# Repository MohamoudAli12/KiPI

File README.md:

# KiPI — DC, AC and Coupled Noise Power Integrity Simulator (Standalone or KiCad Plugin)

**New to power integrity? Read the [Solver Guide](https://drewsum.github.io/KiPI/solver-guide.html)**
([source](docs/solver-guide.html)): what PI analysis is, why it matters, and how KiPI's mesh
and its DC, thermal, AC and coupled noise solvers work.

KiPI is a power and signal integrity analyzer that runs standalone or as a KiCad 9 and 10 IPC
plugin. It has four analysis modes:

* **DC: Voltage Drop.** Define voltage regulators (VRMs), loads (current into pins) and series
  parts (beads, resistors, load switches), then simulate the voltage drop net by net, across
  every copper layer. Inspect voltage, current density, via currents, copper power
  dissipation and (optionally) board temperature in a rotatable 3D view, with PASS/FAIL
  checks for loads, VRMs, vias and temperature, and write an interactive HTML report or a
  PDF.
* **AC: PDN Impedance.** Give the decoupling capacitors RLC models and put probes on a
  device's power pins, then sweep the impedance of the power distribution network (planes,
  vias, mounting and capacitors) over frequency. Check it against a flat or custom target
  impedance, with a calculator that determines the target from the load's transient spec.
* **Coupled Noise: Switcher Noise on Signal Nets.** Treat a buck or boost regulator as an
  aggressor: KiPI builds its switch node, inductor and capacitor ripple waveforms from the
  layout, then works out the noise they couple onto the signal nets you name (the victims)
  through capacitance, mutual inductance and shared ground. Each victim's receiver is
  checked against its logic family's noise margin, with the line held high and held low, and
  the 3D view shows where along its traces the noise couples in.
* **SI: Signal Integrity.** A **Quick Scan** checks every signal net in minutes: impedance
  along each trace and pair, crosstalk to its neighbours, gaps and changes in its return
  path, via stubs and pair skew. A **channel** (a net or differential pair, through its
  series parts) is extracted from field-solved cross-sections and via models into
  S-parameters, TDR, statistical and PRBS eyes with the interface's equaliser, COM, and
  waveforms with generic or IBIS buffers, each checked against the interface (USB, PCIe,
  SATA, HDMI, LVDS, DDR4 and more).

New to KiPI? The **[user guide](docs/help.html)** (also the **Help** button in KiPI, or
**F1**) walks through every button, the workflows and what the results mean. Every
control in KiPI has a tooltip. This README is an overview; the user guide has the details.

**Status: 0.9.3 (alpha, in development)** ([changelog](docs/CHANGELOG.md)). KiPI runs on its own too, with an app launcher that handles dependencies, and imports boards from other layout tools. The author wants to add support for more PCB file formats. If you have an example with good complexity which uses a wide variety of your PCB design tool's features that you are willing to share, please open an [issue](https://github.com/drewsum/KiPI/issues) and attach your PCB file there.

## Install

KiPI runs two ways, from the same folder:

* **As a KiCad plugin**, the main way: click the **KiPI** button in the PCB editor and KiPI
  reads the board open there. For this, the KiPI folder **must be in KiCad's plugins
  folder**, and KiCad installs its dependencies.
* **Standalone**: KiPI started on its own, with its launcher, opens board files and needs
  no KiCad. The folder can be **anywhere**; the launcher installs the dependencies on the
  first start. It opens KiCad 7 to 10 board files (`.kicad_pcb`), ODB++ jobs, HyperLynx
  files (`.hyp`) and KiPI snapshots (`.kipi.json.gz`). Reading CCE files is on the way
  ([#143](https://github.com/drewsum/KiPI/issues/143)).

### As a KiCad plugin

#### Requirements

* **KiCad 9.0 or later.** Developed on KiCad 10 and confirmed on KiCad 9. Before 9.0.3,
  KiCad cannot say which layers a plated pad has copper on, so pads are kept on every layer
  (KiPI warns in its log), and 9.0.0 cannot report net classes.
* **Python 3.10 to 3.13**, the one KiCad runs plugins with (some dependencies have no
  prebuilt packages for Python 3.14 yet).
  * **Windows:** KiCad's own Python 3.11. Nothing to do.
  * **Linux:** KiCad uses the system Python. On a distribution with Python 3.14 (Ubuntu
    26.04, Fedora 43), pip has to compile some packages, which needs
    `sudo apt install build-essential python3-dev` or similar.
  * **macOS:** KiCad bundles Python 3.9, which is too old. Install Python 3.12 (for
    example from python.org or Homebrew) and select it as the **Python interpreter** in
    *Preferences → Plugins*.

#### Steps

1. In KiCad, enable **Preferences → Plugins → Enable KiCad API**.
2. Clone, link (or copy) this repo into your KiCad plugins folder, or uncompress the release source zip. The examples use KiCad 10's
   folder: for KiCad 9, put `9.0` in place of `10.0`. On Windows, KiCad uses your
   *Documents* folder, which may be redirected to OneDrive:

   ```powershell
   $plug = "$([Environment]::GetFolderPath('MyDocuments'))\KiCad\10.0\plugins"
   New-Item -ItemType Junction -Path "$plug\KiPI" -Target "<path to this repo>"
   ```

   On macOS the folder is `~/Documents/KiCad/10.0/plugins`, and on Linux
   `~/.local/share/kicad/10.0/plugins`:

   ```sh
   ln -s "<path to this repo>" ~/Documents/KiCad/10.0/plugins/KiPI          # macOS
   ln -s "<path to this repo>" ~/.local/share/kicad/10.0/plugins/KiPI       # Linux
   ```

   Or, without git, download `KiPI-<version>.zip` from the
   [latest release](https://github.com/drewsum/KiPI/releases/latest) and unzip it into the
   plugins folder, which gives `plugins/KiPI`.

3. Restart the PCB editor. KiCad builds the plugin venv in the background; the first time this
   downloads PySide6 and VTK, so give it a few minutes. The **KiPI** toolbar button appears
   once the venv is ready. If it never appears, right-click the action in
   *Preferences → Plugins* and choose *Recreate Plugin Environment*.

### Standalone

1. Install **Python 3.10 to 3.13** if you do not have one (from
   [python.org](https://www.python.org/downloads/), or your package manager). On Linux, add
   `python3-venv` (Debian, Ubuntu) and, for the setup window, `python3-tk`.
2. Put the KiPI folder anywhere: clone this repo, or unzip `KiPI-<version>.zip` from the
   [latest release](https://github.com/drewsum/KiPI/releases/latest).
3. Start KiPI with its launcher: double-click **`kipi_launcher.pyw`** (Windows), or run

   ```sh
   python kipi_launcher.py                      # or: python kipi_launcher.py <board>.kipi.json.gz
   ```

   On Windows the first start leaves a **KiPI** shortcut next to it. On Linux and macOS, run
   `python3 kipi_launcher.py --create-shortcut` once to add KiPI to the applications menu
   (Linux) or `~/Applications` (macOS).

The first start sets up KiPI. The setup window lists every package KiPI will install with
its size (about 254 MB to download on Windows), and nothing is installed until you click
**Install**. On Windows and Linux x86-64 it also offers
[PARDISO](#optional-faster-solves-on-large-boards-windows-and-linux-x86-64). Everything goes
into an environment of KiPI's own, outside the KiPI folder (`KIPI_HOME` puts it elsewhere):

| | KiPI's environment |
|---|---|
| Windows | `%LOCALAPPDATA%\KiPI` |
| macOS | `~/Library/Application Support/KiPI` |
| Linux | `~/.local/share/kipi` |

Use **Open…** to open a board and **Reload** to read it again. KiCad boards keep the same
setup file standalone and in the plugin. KiPI uses the zone fills saved in the file, so
**fill the zones in KiCad (B) and save** before opening a `.kicad_pcb`. ODB++ jobs and
HyperLynx files share a board's setup when exported next to it with the same name
(`Board.zip`, `Board.hyp`). The [user guide](docs/help.html) lists what each format does
and does not carry.

To change the setup later, use **About → Manage dependencies…** in KiPI, or the launcher:

```sh
python kipi_launcher.py --setup              # the setup window again (add or remove PARDISO)
python kipi_launcher.py --add-pardiso        # or --remove-pardiso, without questions
python kipi_launcher.py --repair             # reinstall everything from scratch
python kipi_launcher.py --reset              # delete KiPI's environment
python kipi_launcher.py --create-shortcut    # add KiPI to the Start menu / app menu / ~/Applications
```

If setup fails, the launcher says why; everything the installer printed is in the `logs`
folder next to the environment.

### Optional: faster solves on large boards (Windows and Linux, x86-64)

If the optional [`pypardiso`](https://pypi.org/project/pypardiso/) package is installed,
KiPI solves with Intel MKL's multithreaded PARDISO solver in place of SciPy's
single-threaded one. On a 645k-unknown rail one solve drops from about 8 s to 1.2 s. Small
boards gain little. It costs about 210 MB of download on Windows (320 MB on Linux) and
there are no MKL packages for macOS or ARM.

The KiCad plugin gets it with its other requirements, installed by KiCad into the plugin's
environment. Standalone, the launcher's first setup installs it by default, with an
opt-out. *About → Manage dependencies…* adds or removes it later (in the plugin, removed it
is also left unused, since KiCad puts it back when it reloads the plugin), and *About → Copy version info* shows which solver is in use. If
PARDISO cannot load, KiPI falls back to SciPy and says so in the log.

## Using KiPI

### 1. Open your board in KiCad

Open your board in the PCB editor and click the **KiPI** toolbar button. KiPI opens in its
own window and reads the board through the KiCad API; the log at the bottom streams each
stage as it runs.

* **Load from KiCad** re-reads the board after you edit it in KiCad, and reloads the saved PI setup.
* **Refill zones** (on by default) refills every zone in KiCad before reading, so the zone
  fills KiPI sees match your current routing. KiPI analyzes filled copper only.
* **Save snapshot… / Open snapshot…** store the extracted board as a file that KiPI can open
  later without KiCad. See example snapshots in the repo to experiment!
* **Power Integrity: DC / AC / Noise** and **Signal Integrity: SI** (the start of the
  toolbar, or **Ctrl+1** to **Ctrl+4**) pick the analysis mode. Readme sections 2 to 5 are DC, the default;
  [section 6](#6-ac-pdn-impedance) covers AC, [section 7](#7-coupled-noise) Coupled Noise and
  [section 8](#8-signal-integrity) Signal Integrity. The VRMs, series links and capacitor
  models are shared by the power modes.
* **Help** (or **F1**) opens the [user guide](docs/help.html) in your browser.

### 2. Pick Power Nets from Netlist

The **Board** panel on the left lists every net in the extracted design. Tick the nets you
want to analyze: only ticked nets can be simulated, and they are offered in the PI setup pin
pickers. **Power & ground only**, **All power** and **None** help pick them, and the ticks
are saved with the setup.

Below that are the **Copper layers**, the **Display** options (color by layer or net, Z
scale, vias, pads, mask, silkscreen, part **3D Models**), and **PI Models**, which marks the
parts of the current analysis in 3D. Clicking a part in 3D selects it in the setup, and the
**Info** box shows whatever you last clicked, with **Select in KiCad** to find it in the PCB
editor.

The **Power tree** toolbar button opens a block diagram of the modelled power network, left
to right in the direction power flows, and can be saved as a PNG.

The **Stackup** toolbar button lists every copper and dielectric layer with its thickness,
material, εr, thermal conductivity and resistivity, with a cross-section drawn to scale.
Untick **Lock to imported values** to try other thicknesses and materials: every analysis
uses the edited stackup.

Drag to rotate, scroll to zoom and shift-drag (or middle-drag) to pan; the
[user guide](docs/help.html#keys) lists every keyboard shortcut.

### 3. Model the Power Distribution System

The **PI setup** panel on the right holds the power tree. Each list has **Add**,
**Duplicate** and **Remove** buttons, and every field has a tooltip. Pins are chosen with a
picker: the net, then the part, then optionally the pin numbers. As you pick pins, KiPI
pre-fills what usually follows from them (a VRM's target voltage from the net name, ground
pins, a series link's other side and a resistor's value), and problems are shown in red.
**Import…** fills the power tree from a Tomachie power-tree file (`<design>.pdn.json`).

**VRMs tab**: one entry per regulator, power input, or ideal supply. A VRM is a **Source**,
**LDO**, **Switcher** or **Isolated** converter, with its output pins and target voltage,
its input pins (which link it to the rail upstream), efficiency or quiescent current, and
optional remote sense, ground pins, load line, dropout, input range, DC accuracy, current
limit and multiple **Phases**. KiPI works out each VRM's input current from what it feeds.

To try it without a design of your own, open the example board in
[`examples/multiphase_buck`](examples/multiphase_buck): a 4-phase 12 V → 0.9 V, 40 A core rail
(`python -m kipi --snapshot examples/multiphase_buck/multiphase_buck.kipi.json.gz`).

**Loads tab**: one entry per consumer: its **Supply pins**, **Current** (split evenly or by
pin group), optional **Ground pins** and a **Tolerance** for PASS/FAIL. **Load models**
(**Model ▾**) save and apply a part's supplies as a YAML file.

**Series links tab**: parts that pass DC from one net to another, such as sense
resistors, ferrite beads, fuses, load switches and 0 Ω links: **Side A pins**, **Side B
pins** and a **Resistance**. **Import SPICE model…** uses the maker's SPICE model of the part
for both DC and AC, including diodes and multi-pin parts such as common-mode chokes.
**In order to assign a series link, the nets on either side must both be defined as power
nets in the net selection pane.**

**Solve tab**: every combined rail, with a checkbox. Untick the rails that are not modeled or
routed yet to solve the rest.

**Mesh tab**: **Max edge** is the largest FEA mesh triangle edge in mm; smaller is more
accurate and slower. **Via plating** sets each kind of via's plating thickness and fill.

**Thermal tab** (off by default): tick **Electro-thermal co-simulation** to make losses heat
the board and the warmer copper become more resistive. Each copper layer has its own
temperature, with heat crossing the laminate and running down vias. Inspired by
[KiCad Thermal Sim](https://github.com/PoeAlex/KiCad_Thermal_Sim) by
[PoeAlex](https://github.com/PoeAlex).

The setup is saved as `<board>.kipi-setup.yml` next to the board when you click **Save** and
every time you solve. It travels with the project and can go into version control. AI agents
can make quick work of power tree modelling by editing this file directly.

### 4. Solve

Click **Solve all**. Every rail is meshed and solved, downstream loads first, so each VRM's
input current includes everything it feeds. Progress streams into the log; **Cancel** stops
the run.

Click **Report** to write an HTML report next to the board, or choose **PDF**. The HTML
report is a single portable file with the summary and every results table, an interactive 3D
view per rail, per-layer voltage and current-density maps, the board temperature map when
thermal is on, and a **User notes** box.

| Summary tables | Interactive 3D per net group |
|---|---|
|  |  |

### 5. Read the results

In the **Results** pane, choose a **net group** and a **field** to show in 3D: **Voltage**,
**Current density** (tick **Arrows** to see the flow), **Power density**, **Via current**
or **Temperature**. Click any point to probe it in the Info box, and set the **Color
scale** to look closer.

| Via current | Temperature |
|---|---|
|  |  |

The result tabs give **Loads** (effective voltage, drop and PASS/FAIL), **VRMs**, **Series
links** (I²R losses), **Vias** ranked by current, **Losses**, **Thermal** and **Notes**.
**Export ▾** writes CSV or ParaView files, and **Save results…** writes a results file that
**Open results…** reloads without solving again.

### 6. AC: PDN impedance

Switch **Mode** to **AC**. The **AC setup** shares the VRMs and series links with DC mode and
adds:

* **Capacitors tab**: RLC models (capacitance, ESL, ESR) for the decoupling capacitors, each
  shared by a group of identical parts, or the maker's SPICE model. **Models from values**
  starts one model per capacitor value. Models can be derated for DC bias, temperature,
  aging and tolerance. **Important**: model capacitors of the same value in different case
  sizes separately.
* **Probes tab**: where to plot the PDN impedance, usually a device's supply and ground pins,
  each with a **flat** or **custom** target. The **Target Impedance/Frequency Calculator**
  works out a flat target from the device's voltage tolerance and load step, following Smith
  et al., ["Power Distribution System Design Methodology and Capacitor Selection for Modern
  CMOS Technology"](https://doi.org/10.1109/6040.784476), IEEE Trans. Adv. Packaging, 1999.
  Targets apply above the VRM's **Control loop bandwidth**.
* **Sweep tab**: frequency range and resolution, and the capacitor deratings.
* **Mesh tab**: mesh size and minimum edge at plated holes.

| Capacitor models | Target calculator |
|---|---|
|  |  |

Pick the **Rail** and **Ground** and click **Solve rail**. The rail's copper and its ground
are field-solved, so plane resistance, spreading inductance, plane capacitance, cavity
resonances and via inductance all come from the layout; the capacitors and series links are
attached at every frequency. The VRM is not modeled as an impedance (the open-loop PDN).
**Important:** AC analysis is a massive compute problem. Many probes and a finer mesh
increase simulation time dramatically.

The **Impedance** tab plots |Z| against frequency for every probe, with its target, and a
cursor to read values. The **Board map** tab shows the mesh, probes and capacitors, and the
**Transient** tab estimates each probe's undershoot and overshoot for its load step.
**Report**, **Export CSV…** and **Save results…** work as in DC mode.

### 7. Coupled Noise

Switch **Mode** to **Noise**. The **Coupled Noise setup** treats one of the setup's
**Switcher** VRMs as an *aggressor* and the signal nets you name as *victims*. The
screenshots below are the `examples/validation/coupled_noise` example: a 12 V to 1.8 V,
1 MHz buck over a ground plane, with three victims. Open its snapshot to try it.

* **Aggressors tab**: **Add** makes an aggressor from a switcher VRM and fills it in from the
  board: the switching device, inductor, switch node and capacitors. Give the switching
  frequency and edge times; datasheet values such as Coss and Qrr are optional. KiPI traces
  each capacitor's hot loop through the copper for its inductance and its coupling.
* **Victims tab**: each victim is a net with its driver and receiver pins and a **Type**
  (CMOS, open drain, terminated, LVDS, analog input or undriven) and **Logic level**, which
  set its loading and noise margin.
* **Capacitors tab**: the same capacitor models as AC mode.
* **Settings tab**: harmonics, damping, victim resolution and the **Board model**, the slow
  but more accurate field model of the converter's copper (untick it for a quick look).

Pick the **Aggressor** and click **Solve**. Tick **Scan nearby nets** to also check every
signal net near the aggressor. The **Waveforms** tab plots the switch node with its ringing,
the inductor and capacitor currents and the rail ripple, in time or as a spectrum.

The **Results** table lists each victim's peak noise at its receiver, its margin, the
dominant mechanism and PASS or FAIL. **Victim noise** plots the noise, as a whole or by
mechanism (capacitive, inductive, common ground).

**Victim held high and low** draws the noise riding on the receiver's high and low levels
against its thresholds.

**Coupling in 3D** colors the selected victim's traces by their share of the peak noise, so
the pieces to move stand out. **Hot loops in 3D** draws the capacitor loops' current, and
**Fields in 3D** the H and E fields over the board, with near-field hotspots and a first
radiated estimate against CISPR 32 class B. Victims crossing a split in their reference
plane are noted.

The mechanisms point to different fixes: capacitive noise comes from the switch node's
dV/dt, inductive noise from the hot loop's dI/dt and common noise from the switching
current's return. **Report** and **Save results…** work as in the other modes.

### 8. Signal Integrity

Switch **Mode** to **SI** (**Ctrl+4**). The **Signal Integrity setup** has four tabs. To
try it, open `examples/signal_integrity/signal_integrity.kipi.json.gz`: a clock net through
a series resistor and a USB pair changing layers through vias, with a channel set up for
each.

* **Quick Scan**: **Scan** cuts every signal net (or only the nets ticked in **Board**) into
  short sections and field-solves each cross-section with its neighbours. Each net gets
  PASS, WARN or FAIL for its impedance (Z0, or Zdiff for pairs found by name: `_P`/`_N`,
  `+`/`-`, `DP`/`DM`), its worst crosstalk coefficient, any length with no reference plane
  or crossing a plane's gap, layer changes without a return via nearby, via stubs that
  resonate in band, and pair skew. **Impedance in 3D** colors the traces by how far they
  are from target. **Make a channel** turns the selected net into a channel. Slow control
  nets (enables, resets, LEDs, I²C, JTAG) are left out unless **Slow nets** is ticked. Cuts
  that come out alike are solved once, in parallel on the CPU's cores: a 6-layer board with
  about 400 signal nets takes a few minutes, and a rescan seconds.
* **Channels**: a channel is a net or a pair, followed through series resistors and
  AC-coupling capacitors to its receiver. **Add bus…** makes one for each net between a
  transmitter and a receiver part (a DDR byte lane, an ADC's lanes), with the neighbours as
  aggressors. Pick its **Interface** (rate, swing, edges,
  terminations, equaliser and limits come from it, and any can be overridden) and its
  **buffers**: generic ones, or a model from a manufacturer's **IBIS** file at a corner.
  **Aggressors** add their near- and far-end crosstalk.
* **Results**: after **Solve**, the checks (impedance, insertion and return loss at
  Nyquist, mode conversion, skew, the eye against the receiver mask, COM, overshoot,
  ringback, monotonic edges, crosstalk) and the **SI plots** tab: the eye (statistical at
  the target BER with the best equaliser, or the raw or PRBS eye), TDR, S-parameters,
  waveforms at the dies and the pulse response. **Export Touchstone…** writes the channel's
  `.s2p`/`.s4p`, and **Export SPICE…** a passive rational model of it as a SPICE subcircuit
for any circuit simulator; **Report** and **Save results…** work as in the other modes.
* **Settings**: section length, etch, copper roughness (Hammerstad, Groisse or Huray), the
  sweep and the scan's limits.

### Tips and troubleshooting

* **A load shows DISCONNECTED** usually means unrouted copper, an unfilled zone, or a
  missing series link for a part between two power nets.
* **Unexpected voltage drop:** thermal reliefs, necked traces, via counts and anti-pads in
  planes dominate DC drop; the Current density view with Arrows shows the bottleneck.
* **Slow solves:** raise **Max edge**, or analyze fewer nets at a time. On Intel x86, install
  the PARDISO solver (above).
* **"KiPI works with one KiCad at a time"** although only one is open: a KiCad that did not
  exit cleanly may still be running; end it in the task manager.
* **Logs:** each session writes to `kipi/kipi-<date>-<time>-<pid>.log` in the temporary
  folder, with a matching `.crash.log`. Attach both, and **About → Copy version info**, to
  bug reports. The [user guide](docs/help.html) has more troubleshooting.
* **Have Fun:** The author asks that you share what projects this package has simulated, and what power integrity issues you have found with it. Conductor simulation gives incredible insight into how PCBs actually function in practice. See what happens when you pump 10 amps into a 5 mil trace with the temperature results view.

## Development

From a checkout, KiPI runs standalone, or as the plugin against the running PCB editor:

```powershell
python -m venv --system-site-packages .venv   # use KiCad's bundled python.exe
.venv\Scripts\pip install -r requirements.txt -r requirements-dev.txt
.venv\Scripts\python -m kipi tests\data\synthetic.kipi.json   # standalone, opening a board
$env:KIPI_HOST = "plugin"; .venv\Scripts\python -m kipi        # the plugin: connect to KiCad
.venv\Scripts\python -m kipi --dump board.kipi.json.gz   # extract from KiCad only, no window
.venv\Scripts\python -m pytest tests
.venv\Scripts\ruff check .                    # lint, as CI does (ruff check . --fix fixes most)
```

`requirements.txt` is what KiCad installs into the plugin's venv, and
`requirements-standalone.txt` what the launcher installs; `tests/core/test_requirements.py`
keeps them in step with `pyproject.toml`. After changing them, run
`python .github/scripts/dep_sizes.py`.

The tests follow the package (`tests/core`, `tests/dc`, `tests/ac`, `tests/noise`,
`tests/sources`, `tests/gui`, `tests/scripts`). `tests/accuracy` solves the boards in
[`examples/validation`](examples/validation) and compares the results with hand
calculations, to help gain confidence that an open-source tool can compare to professional
tools:

| Board | Checks |
|---|---|
| `skinny_traces` | 0.15 mm and 0.1 mm tracks on outer and inner layers (ρL/wt), an arc track (annular sector) |
| `right_angle` | an L route and a Z route: 0.5587 squares per right-angle corner |
| `layer_change` | a strip dropping from F.Cu to In2.Cu through a row of vias: barrels in parallel, current crowding, equal sharing |
| `planes` | two pads on a disc-shaped inner plane (method of images); one strip on two layers of different weights |
| `power_chain` | source, switcher, ferrite series link and remote-sensed LDO over a ground strip: every voltage and current |
| `ac_plane` | plane-pair capacitance ε₀εrA/h and the first cavity resonance c/(2a√εr) |
| `ac_decap` | a mounted capacitor as a series RLC: low-frequency capacitance, mounted inductance, ESR at resonance |
| `ac_ferrite` | a ferrite (R + L link) feeding a small plane: lumped impedance and its LC resonance |

After changing a board there, rerun `python examples/validation/make_boards.py [name]` (or
`python examples/multiphase_buck/make_board.py` for the example) and commit its files.

CI runs ruff and the test suite for every push and pull request on Windows, Linux (Python
3.10 to 3.13) and macOS; the accuracy tests run for pull requests into `main`.
`tests/helpers/kicad_fake.py` stands in for each KiCad version from 9.0.0 to 10.0.6.

### Codebase Layout

| Path | Purpose |
|---|---|
| `kipi_entry.py`, `plugin.json` | KiCad IPC plugin action (runs KiPI as the plugin) |
| `kipi/__main__.py` | `python -m kipi` / `kipi`: standalone, or the plugin with `KIPI_HOST=plugin` |
| `kipi_launcher.py`, `.pyw` | Standalone launcher: sets up KiPI's environment on the first start, then starts KiPI in it |
| `kipi/launcher/` | The launcher itself, standard library only: environment, Python discovery, package list, installer and setup screens |
| `kipi/host.py` | Plugin or standalone: how KiPI was started |
| `kipi/core/` | Shared by every analysis: board model, copper geometry, meshing, sparse solvers, 3D meshes, progress reporting |
| `kipi/sources/` | Where boards come from: the running KiCad (IPC), `.kicad_pcb` files, ODB++, HyperLynx and snapshots |
| `kipi/dc/` | DC analysis: conduction FEM, power-tree setup and solve, thermal, reports, results views and panel |
| `kipi/ac/` | AC analysis: PDN impedance over frequency, field solver and sweep, targets, transient, report and panel |
| `kipi/noise/` | Coupled Noise analysis: waveforms, hot loop parasitics, coupling extraction, victim solves, report and panel |
| `kipi/si/` | Signal Integrity: 2D cross-section field solver, via models, channel circuit, S-parameters, IBIS, transient, eyes and equalisers, Quick Scan, report and panel |
| `kipi/gui/` | PySide6 application shell shared by every mode: main window, mode switch, 3D viewer, worker threads, About and Help |
| `docs/help.html` | The user guide opened by **Help**; a single offline HTML file |
| `docs/solver-guide.html` | The Solver Guide: PI background and how the solvers work |
| `kipi/compat.py` | Opens results files saved by earlier versions, from before modules moved |
| `examples/` | Example boards as snapshots with their PI setups, and the scripts that generate them |

## License

KiPI is free software: you can redistribute it and/or modify it under the terms of the
[GNU General Public License](LICENSE) as published by the Free Software Foundation, either
version 3 of the License, or (at your option) any later version. It is distributed WITHOUT
ANY WARRANTY; see the license for details. Copyright © 2026 Drew Maatman.

**Note on the mesher.** KiPI meshes copper with Jonathan Shewchuk's
[Triangle](https://www.cs.cmu.edu/~quake/triangle.html), through the
[`triangle`](https://pypi.org/project/triangle/) Python package. Triangle is not open source
in the OSI sense. Its author's terms allow free use and redistribution, but it **may not be
sold or included in commercial products without a license from its author**. Using KiPI for
your own design work is fine. The meshing code is isolated in `kipi/core/mesh/` for this reason.

The other dependencies are under permissive licenses, apart from PySide6 (LGPL-3.0). All of
them are compatible with the GPL.

The author of KiPI prohibits the package from inclusion in commercial software. Use it, fork it, and modify it to your heart's content.

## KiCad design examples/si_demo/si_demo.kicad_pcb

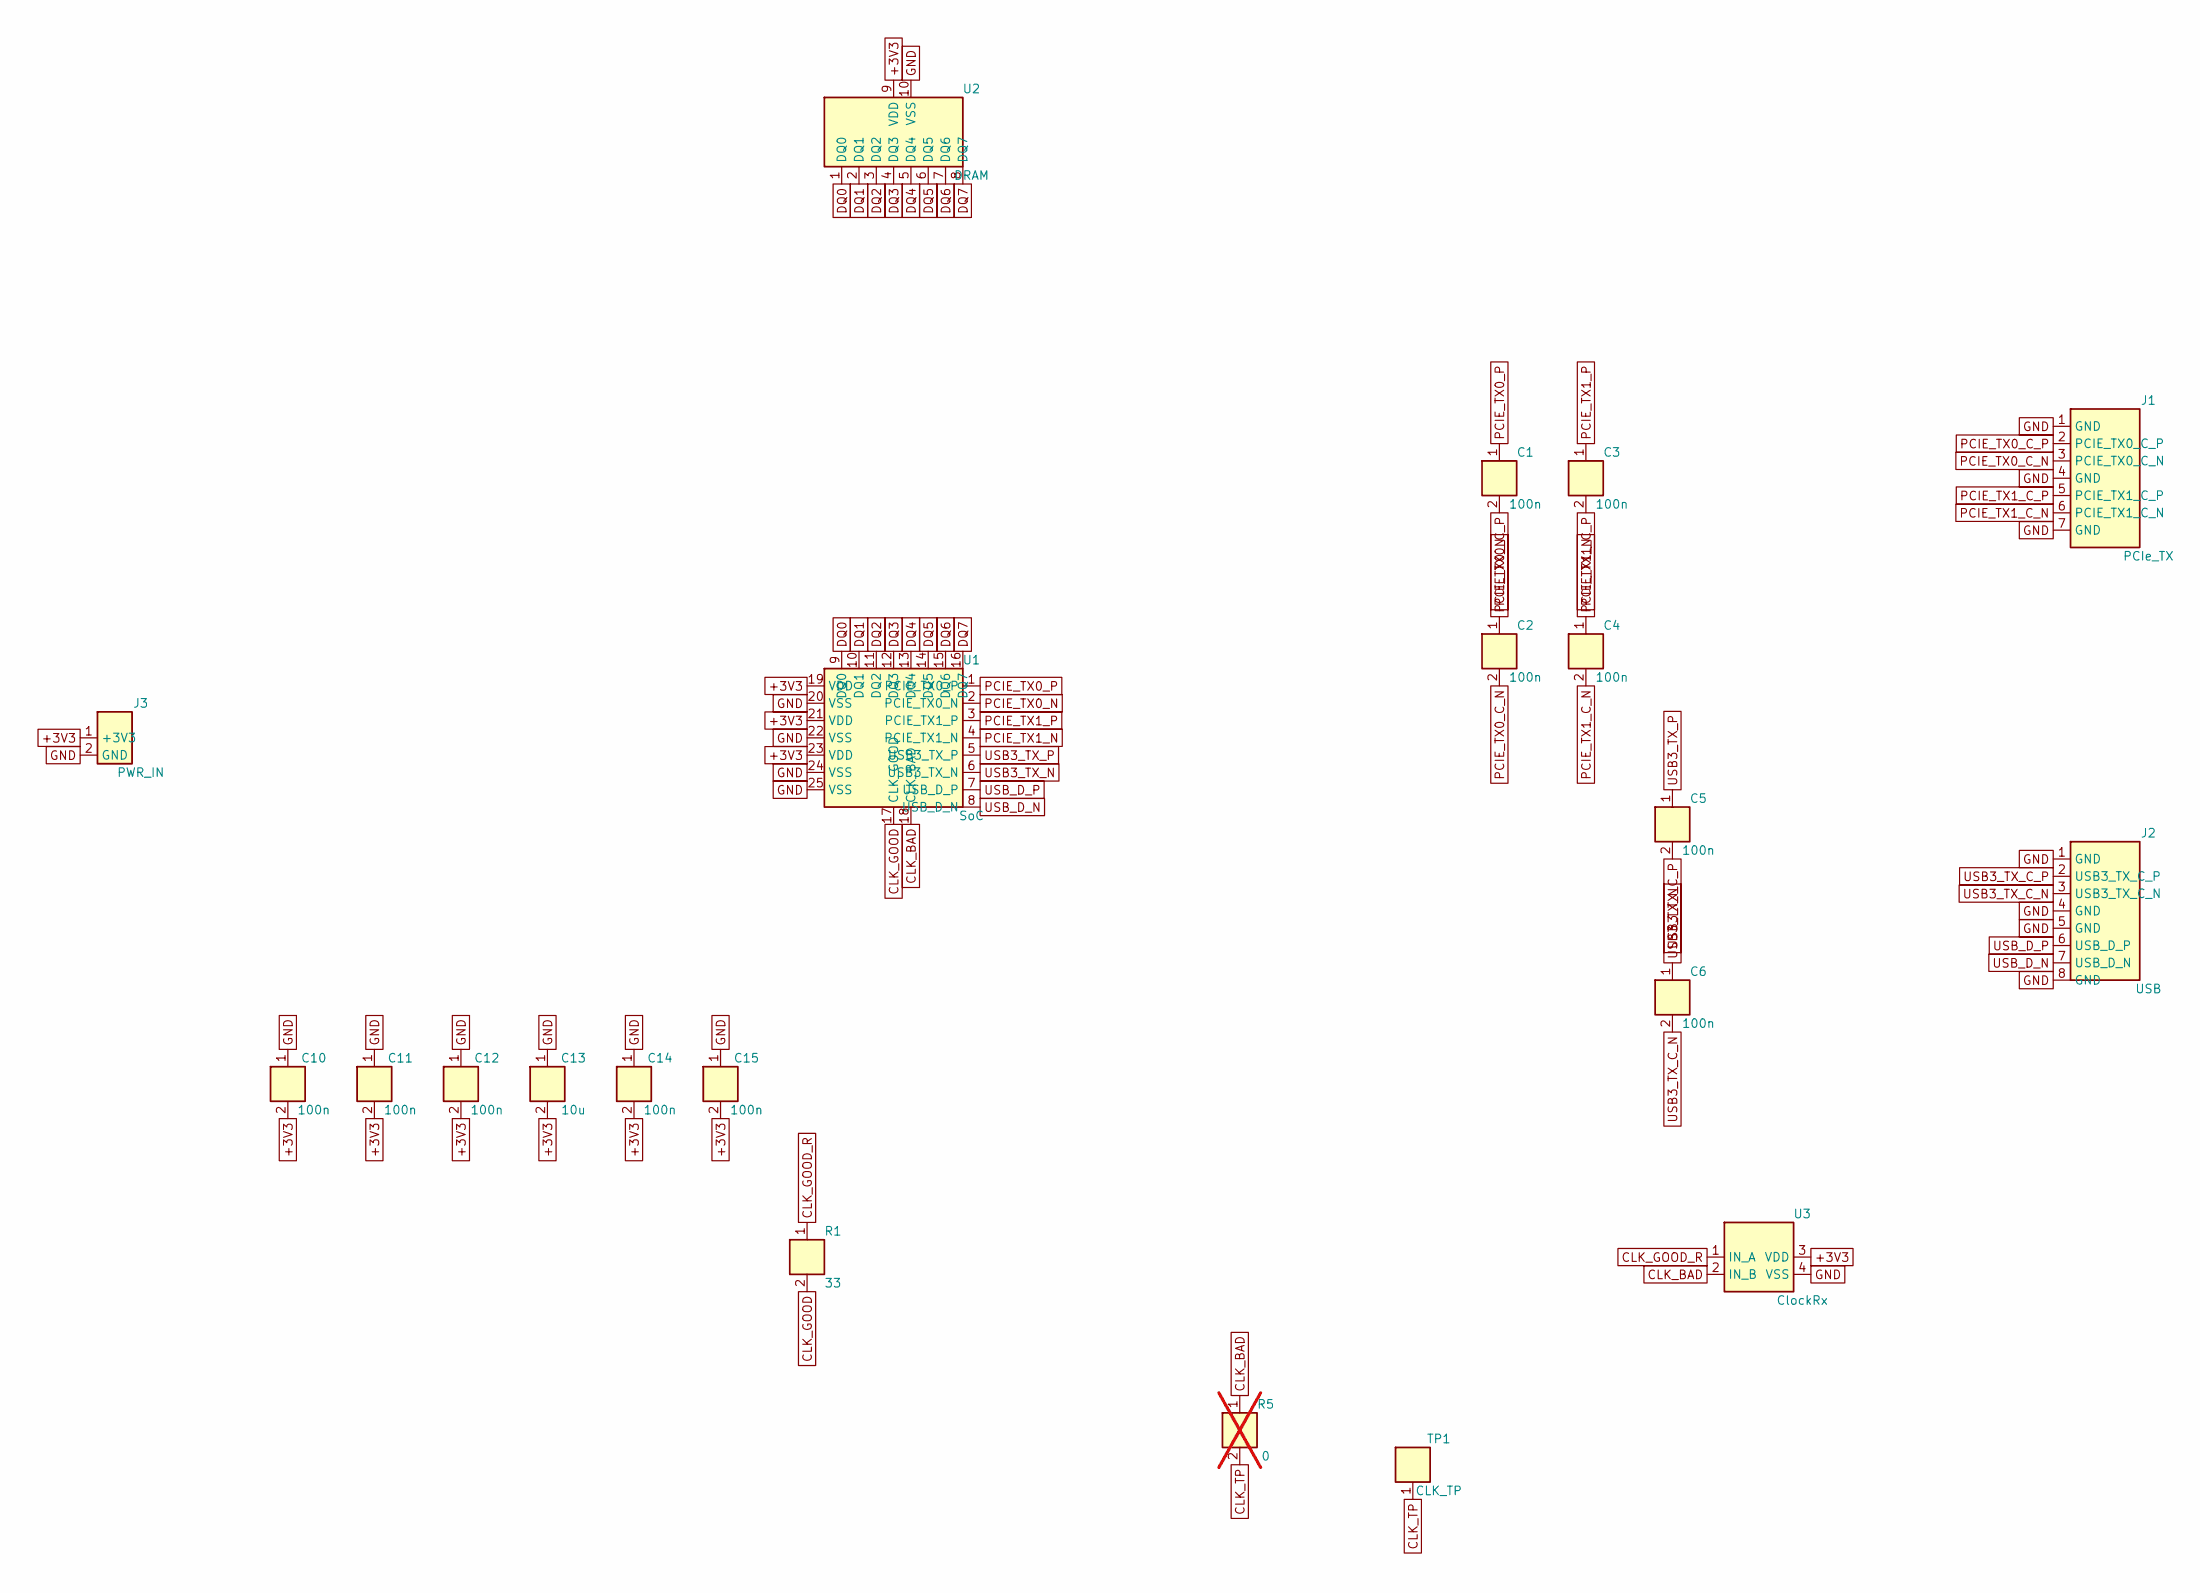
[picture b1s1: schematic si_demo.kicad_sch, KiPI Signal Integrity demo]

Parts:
C1, C2, C5, C6: 100n; C_0201
C3, C4, C10, C11, C12, C14, C15: 100n; C_0402
C13: 10u; C_0402
J1: PCIe_TX; Conn_PCIe
J2: USB; Conn_USB
J3: PWR_IN; PinHeader_1x02
R1: 33; R_0402
R5: 0; R_0402; not fitted
TP1: CLK_TP; TestPad
U1: SoC; SoC_QFN
U2: DRAM
U3: ClockRx

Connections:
+3V3: C10.2, C11.2, C12.2, C13.2, C14.2, C15.2, J3.1 (+3V3), U1.19 (VDD), U1.21 (VDD), U1.23 (VDD), U2.9 (VDD), U3.3 (VDD)
CLK_BAD: R5.1, U1.18 (CLK_BAD), U3.2 (IN_B)
CLK_GOOD: R1.2, U1.17 (CLK_GOOD)
CLK_GOOD_R: R1.1, U3.1 (IN_A)
CLK_TP: R5.2, TP1.1
DQ0: U1.9 (DQ0), U2.1 (DQ0)
DQ1: U1.10 (DQ1), U2.2 (DQ1)
DQ2: U1.11 (DQ2), U2.3 (DQ2)
DQ3: U1.12 (DQ3), U2.4 (DQ3)
DQ4: U1.13 (DQ4), U2.5 (DQ4)
DQ5: U1.14 (DQ5), U2.6 (DQ5)
DQ6: U1.15 (DQ6), U2.7 (DQ6)
DQ7: U1.16 (DQ7), U2.8 (DQ7)
GND: C10.1, C11.1, C12.1, C13.1, C14.1, C15.1, J1.1 (GND), J1.4 (GND), J1.7 (GND), J2.1 (GND), J2.4 (GND), J2.5 (GND), J2.8 (GND), J3.2 (GND), U1.20 (VSS), U1.22 (VSS), U1.24 (VSS), U1.25 (VSS), U2.10 (VSS), U3.4 (VSS)
PCIE_TX0_C_N: C2.2, J1.3 (PCIE_TX0_C_N)
PCIE_TX0_C_P: C1.2, J1.2 (PCIE_TX0_C_P)
PCIE_TX0_N: C2.1, U1.2 (PCIE_TX0_N)
PCIE_TX0_P: C1.1, U1.1 (PCIE_TX0_P)
PCIE_TX1_C_N: C4.2, J1.6 (PCIE_TX1_C_N)
PCIE_TX1_C_P: C3.2, J1.5 (PCIE_TX1_C_P)
PCIE_TX1_N: C4.1, U1.4 (PCIE_TX1_N)
PCIE_TX1_P: C3.1, U1.3 (PCIE_TX1_P)
USB3_TX_C_N: C6.2, J2.3 (USB3_TX_C_N)
USB3_TX_C_P: C5.2, J2.2 (USB3_TX_C_P)
USB3_TX_N: C6.1, U1.6 (USB3_TX_N)
USB3_TX_P: C5.1, U1.5 (USB3_TX_P)
USB_D_N: J2.7 (USB_D_N), U1.8 (USB_D_N)
USB_D_P: J2.6 (USB_D_P), U1.7 (USB_D_P)

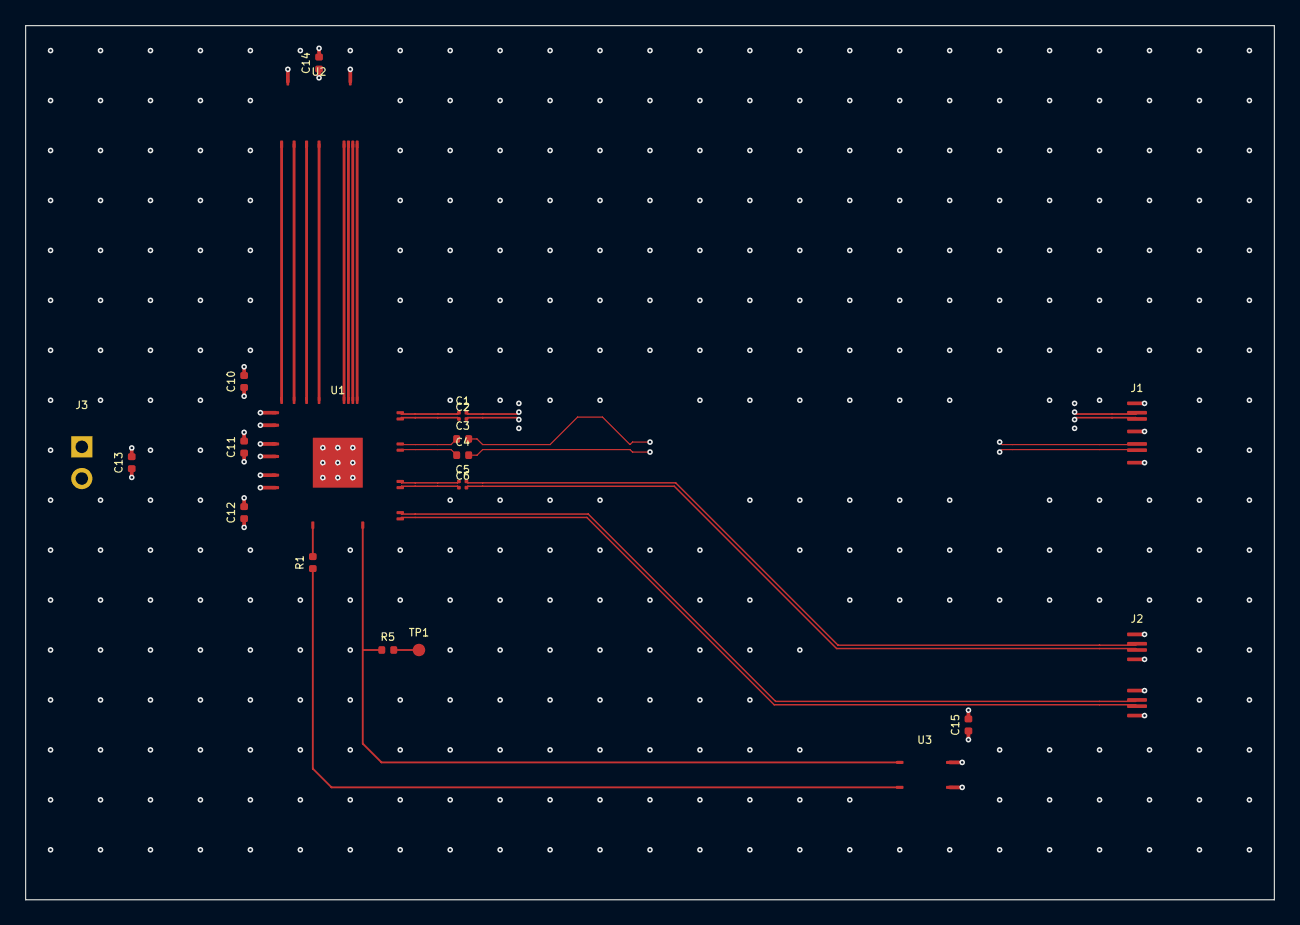
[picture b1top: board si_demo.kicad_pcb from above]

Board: 6 copper layers, 100.0 x 70.0 mm, 21 parts (0 on the bottom side), 28 nets.

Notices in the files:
README.md:
License: GPL v3
